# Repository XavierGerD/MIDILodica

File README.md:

# MIDILodica

## What is the MIDILodica?

The MIDILodica is a breath-controlled, 3D printed, open-source MIDI device that features a pressure sensor, 35 reassignable note buttons, a softpot strip potentiometer, full menu navigation with a 320x172 screen, and underside button for additional MIDI and octave manipulation. This repository contains all the files needed to 3D print and manufacture the MIDILodica.

To accomplish this project, you will need:

- Basic knowledge of the Arduino IDE.
- Basic knowledge of and equipment for soldering.
- Access to a 3D printer.
- All the electronic parts listed below.

</br>

## Parts list

To build the MIDILodica, you will need the following:

- **40 x TL1105SPF160Q Tactile Switch** (can be substituted with TL1240NQ1JBLK if you don't have access to a 3D printer)
- **1x Adafruit 320x172 TFT Display - ST7789 (part no. 5393)** (with headers)
- **1x Arduino Micro** (with headers)
- **40x 1N4148 Through-hole diodes**
- **1x 10k through-hole resistor**
- **1x ABPDANT005PGAA5 Honeywell pressure sensor**
- **1x SEN-08680 50mm Softpot**
- **1x 66226-003LF 3pos clincher** (to replace the Softpot headers)
- **3x Male to Female jumper cables OR 1x 3pos Male to Female jumper cable**
- **1x 3pos right angle header** (to hold the sensor breakout board)
- **6x M2x20 screws** (for the housing)
- **4x M2x8 screws** (for the strip pot plate)

You will also need to obtain TWO printed circuit boards (PCB) with a PCB manufacturing service. The first one is the main board, which has all the buttons and breakout boards. The second PCB holds the sensor, and is attached at a 90 degree angle using the 3pos right angle header. The required files are in a .zip in the `/manufacturing/gerber` folder. If you wish to modify these boards, the `.sch` and `.brd` files are available in the `/manufacturing` folder.

</br>

## License

The project is under the GNU General Public License v3.0.

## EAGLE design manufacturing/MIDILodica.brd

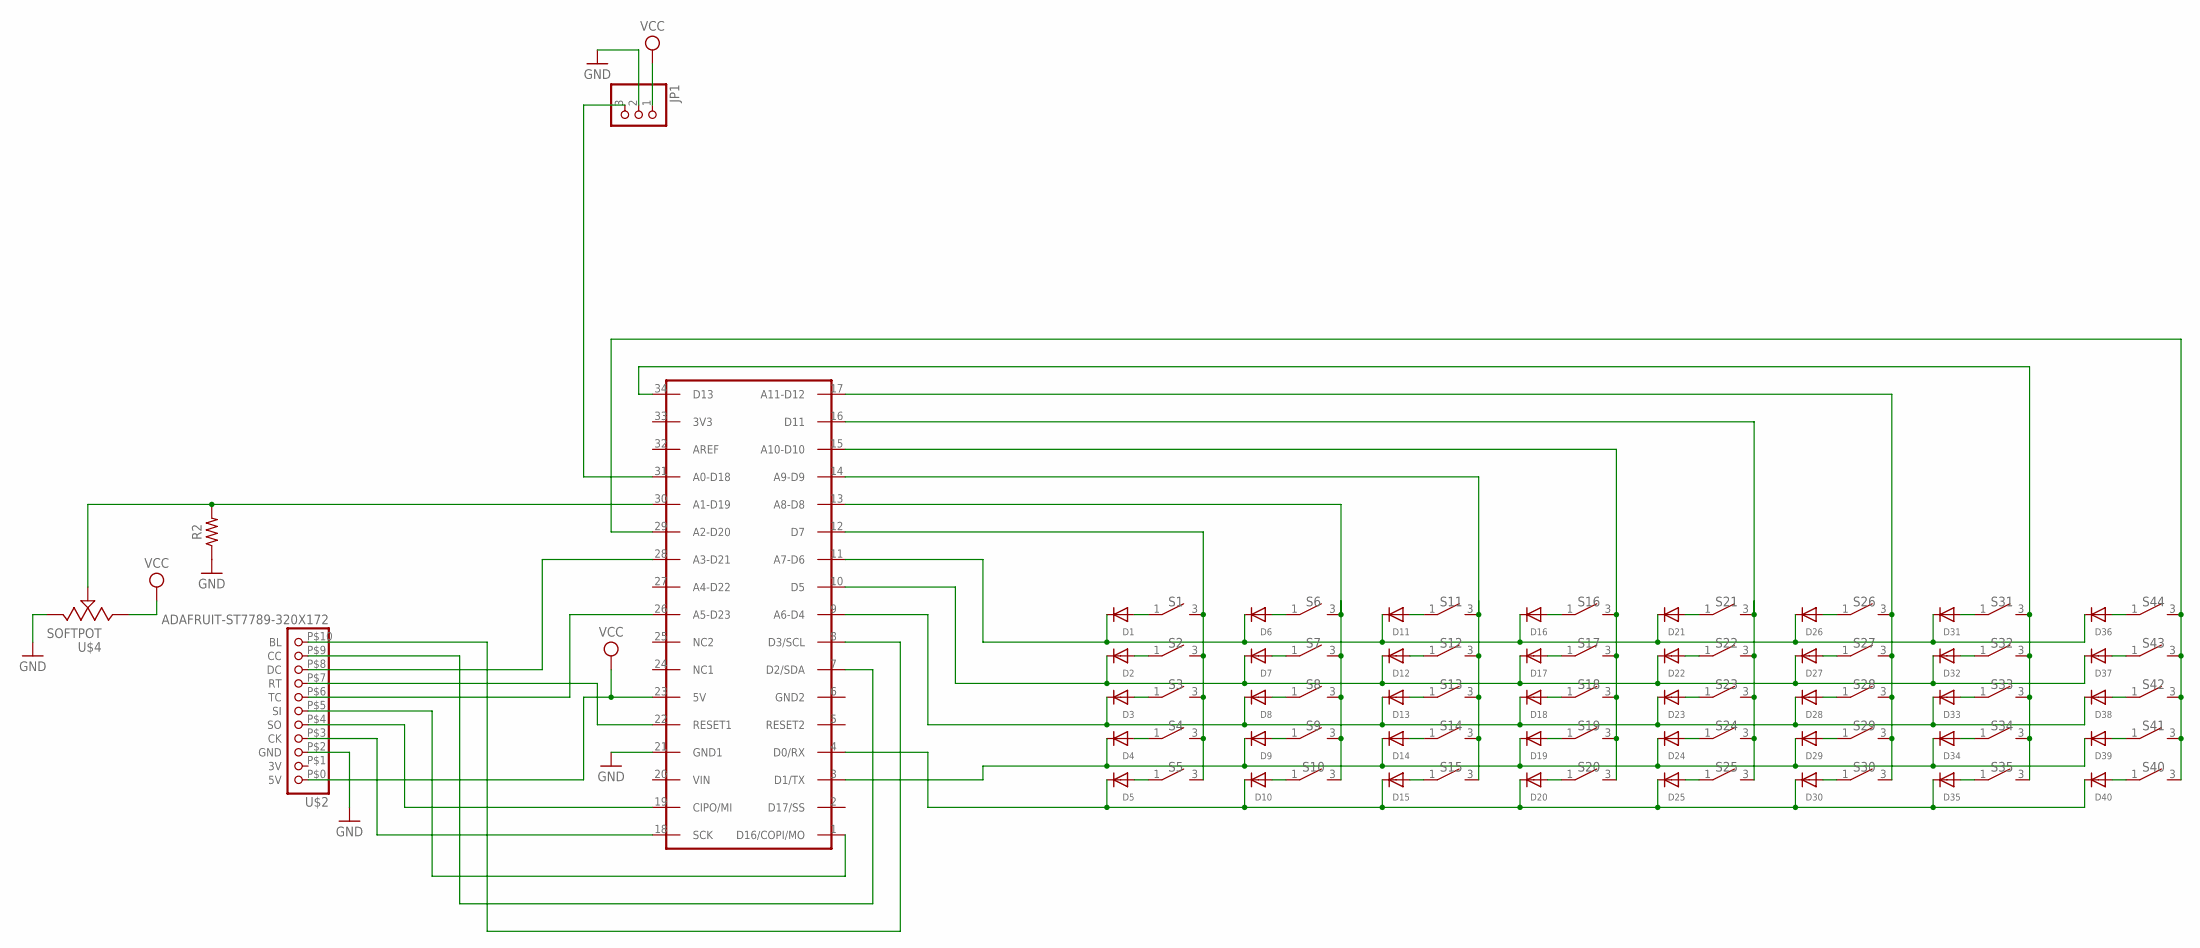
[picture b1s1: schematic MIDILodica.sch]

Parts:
D1, D2, D3, D4, D5, D6, D7, D8, D9, D10, D11, D12, D13, D14, D15, D16, D17, D18, D19, D20, D21, D22, D23, D24, D25, D26, D27, D28, D29, D30, D31, D32, D33, D34, D35, D36, D37, D38, D39, D40: DIODEDO-1N4148; DO-1N4148
JP1: PINHD-1X3; 1X03
R2: R-US_AXIAL-7.2MM-PITCH; RESAD724W46L381D178B
S1, S2, S3, S4, S5, S6, S7, S8, S9, S10, S11, S12, S13, S14, S15, S16, S17, S18, S19, S20, S21, S22, S23, S24, S25, S26, S27, S28, S29, S30, S31, S32, S33, S34, S35, S40, S41, S42, S43, S44: TL1105SPF160Q
U$1: ARDUINO_MICRO; ARDUINO-MICRO
U$2: ADAFRUIT-ST7789-320X172
U$4: SOFTPOT; SOFTPOT-1

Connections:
5V+: JP1.1, U$1.23 (5V), U$2.P$0 (5V), U$4.1
GND: JP1.2, R2.1, U$1.21 (GND1), U$2.P$2 (GND), U$4.3
unnamed: R2.2, U$1.30 (A1-D19), U$4.2
unnamed: JP1.3, U$1.31 (A0-D18)
unnamed: D25.A, S25.1
unnamed: D24.A, S24.1
unnamed: D23.A, S23.1
unnamed: U$1.26 (A5-D23), U$2.P$6 (TC)
unnamed: D4.C, D9.C, D14.C, D19.C, D24.C, D29.C, D34.C, D39.C, U$1.3 (D1/TX)
unnamed: D22.A, S22.1
unnamed: D39.A, S41.1
unnamed: D38.A, S42.1
unnamed: D37.A, S43.1
unnamed: D1.A, S1.1
unnamed: D2.A, S2.1
unnamed: D3.A, S3.1
unnamed: D4.A, S4.1
unnamed: D5.A, S5.1
unnamed: D10.A, S10.1
unnamed: D9.A, S9.1
unnamed: D8.A, S8.1
unnamed: D7.A, S7.1
unnamed: D6.A, S6.1
unnamed: D36.A, S44.1
unnamed: D21.A, S21.1
unnamed: S40.3 (2), S41.3 (2), S42.3 (2), S43.3 (2), S44.3 (2), U$1.29 (A2-D20)
unnamed: D30.A, S30.1
unnamed: D29.A, S29.1
unnamed: D28.A, S28.1
unnamed: U$1.22 (RESET1), U$2.P$7 (RT)
unnamed: D27.A, S27.1
unnamed: D26.A, S26.1
unnamed: U$1.28 (A3-D21), U$2.P$8 (DC)
unnamed: D35.A, S35.1
unnamed: D34.A, S34.1
unnamed: D11.A, S11.1
unnamed: D12.A, S12.1
unnamed: D13.A, S13.1
unnamed: D14.A, S14.1
unnamed: D15.A, S15.1
unnamed: D20.A, S20.1
unnamed: D19.A, S19.1
unnamed: D18.A, S18.1
unnamed: D17.A, S17.1
unnamed: D16.A, S16.1
unnamed: D33.A, S33.1
unnamed: D32.A, S32.1
unnamed: D31.A, S31.1
unnamed: U$1.18 (SCK), U$2.P$3 (CK)
unnamed: U$1.19 (CIPO/MI), U$2.P$4 (SO)
unnamed: U$1.7 (D2/SDA), U$2.P$9 (CC)
unnamed: U$1.8 (D3/SCL), U$2.P$10 (BL)
unnamed: U$1.1 (D16/COPI/MO), U$2.P$5 (SI)
unnamed: D1.C, D6.C, D11.C, D16.C, D21.C, D26.C, D31.C, D36.C, U$1.11 (A7-D6)
unnamed: D2.C, D7.C, D12.C, D17.C, D22.C, D27.C, D32.C, D37.C, U$1.10 (D5)
unnamed: D3.C, D8.C, D13.C, D18.C, D23.C, D28.C, D33.C, D38.C, U$1.9 (A6-D4)
unnamed: D5.C, D10.C, D15.C, D20.C, D25.C, D30.C, D35.C, D40.C, U$1.4 (D0/RX)
unnamed: D40.A, S40.1
unnamed: S1.3 (2), S2.3 (2), S3.3 (2), S4.3 (2), S5.3 (2), U$1.12 (D7)
unnamed: S6.3 (2), S7.3 (2), S8.3 (2), S9.3 (2), S10.3 (2), U$1.13 (A8-D8)
unnamed: S11.3 (2), S12.3 (2), S13.3 (2), S14.3 (2), S15.3 (2), U$1.14 (A9-D9)
unnamed: S16.3 (2), S17.3 (2), S18.3 (2), S19.3 (2), S20.3 (2), U$1.15 (A10-D10)
unnamed: S21.3 (2), S22.3 (2), S23.3 (2), S24.3 (2), S25.3 (2), U$1.16 (D11)
unnamed: S26.3 (2), S27.3 (2), S28.3 (2), S29.3 (2), S30.3 (2), U$1.17 (A11-D12)
unnamed: S31.3 (2), S32.3 (2), S33.3 (2), S34.3 (2), S35.3 (2), U$1.34 (D13)

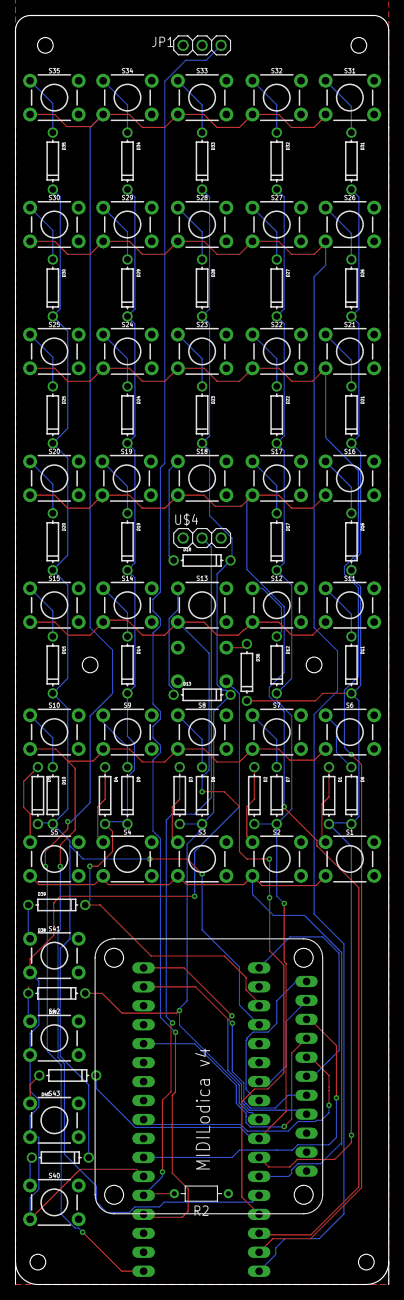
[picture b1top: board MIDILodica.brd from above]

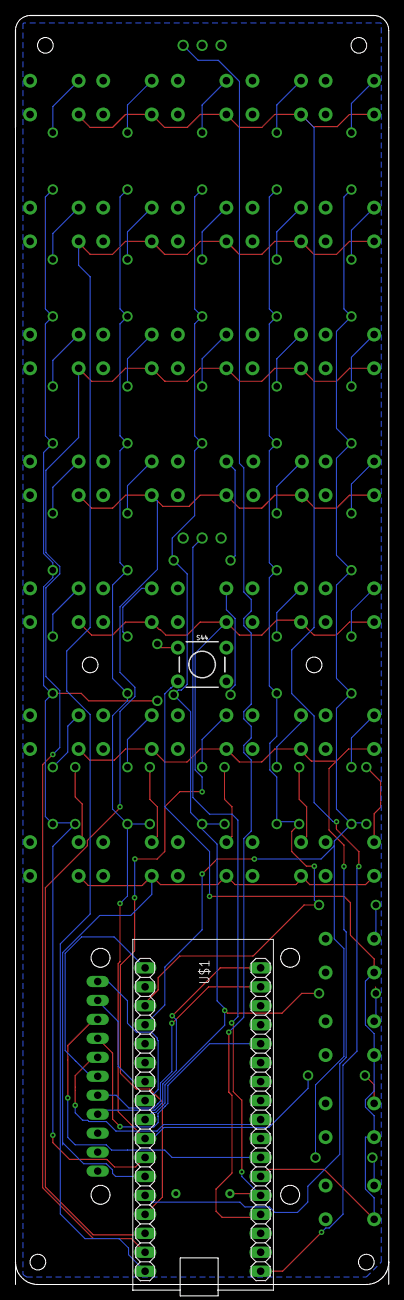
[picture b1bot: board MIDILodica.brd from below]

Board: 2 copper layers, 50.0 x 170.0 mm, 85 parts (2 on the bottom side), 65 nets.

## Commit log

2023-05-14 Init
2023-05-16 Small directory fix
2023-05-16 Small bug fix
2023-05-16 Create LICENSE
2023-05-17 Better documentation
2023-05-17 Markdown fix
2023-05-17 More arkdown fixes
2023-05-17 Sensor board schematics, board and gerber
